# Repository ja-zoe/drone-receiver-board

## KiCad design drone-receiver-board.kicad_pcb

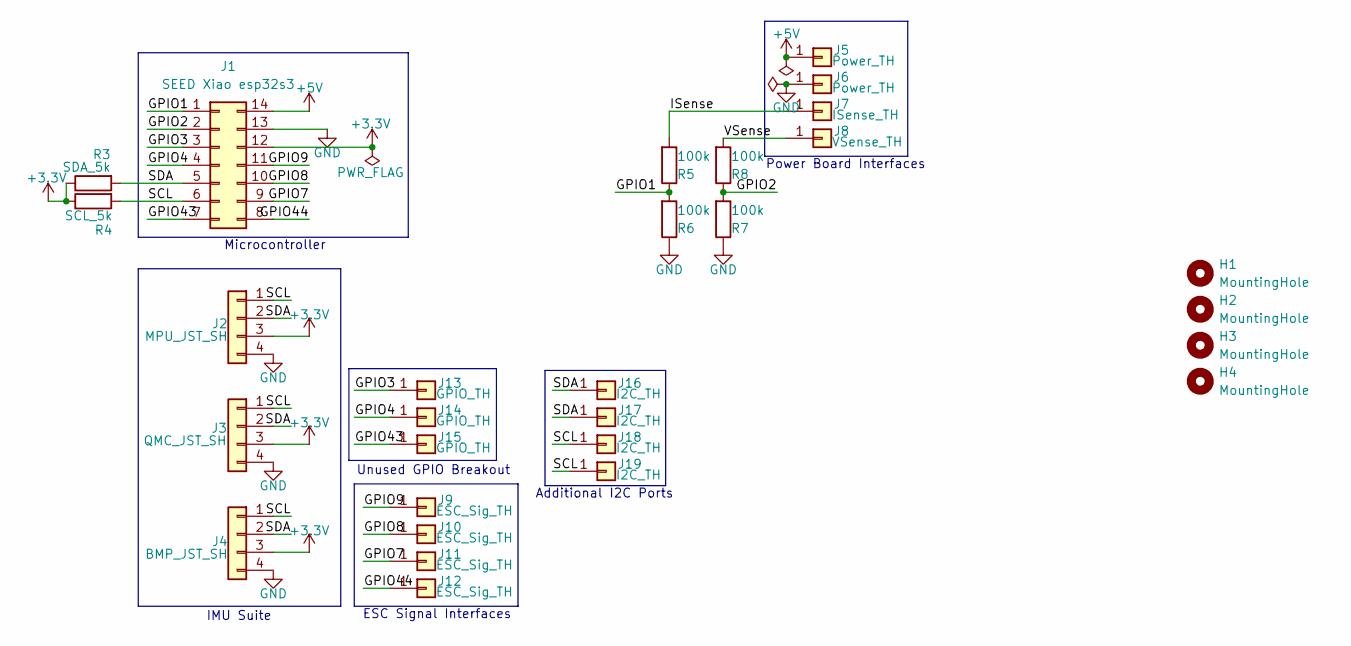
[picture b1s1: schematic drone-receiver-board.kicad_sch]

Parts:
H1, H2, H3, H4: MountingHole; MountingHole_2.2mm_M2
J1: SEED Xiao esp32s3; xiao_esp32c3
J2: MPU_JST_SH; JST_SH_SM04B-SRSS-TB_1x04-1MP_P1.00mm_Horizontal
J3: QMC_JST_SH; JST_SH_SM04B-SRSS-TB_1x04-1MP_P1.00mm_Horizontal
J4: BMP_JST_SH; JST_SH_SM04B-SRSS-TB_1x04-1MP_P1.00mm_Horizontal
J5, J6: Power_TH; SolderWire-0.1sqmm_1x01_D0.4mm_OD1mm
J7: ISense_TH; SolderWire-0.1sqmm_1x01_D0.4mm_OD1mm
J8: VSense_TH; SolderWire-0.1sqmm_1x01_D0.4mm_OD1mm
J9, J10, J11, J12: ESC_Sig_TH; SolderWire-0.1sqmm_1x01_D0.4mm_OD1mm
J13, J14, J15: GPIO_TH; SolderWire-0.1sqmm_1x01_D0.4mm_OD1mm
J16, J17, J18, J19: I2C_TH; SolderWire-0.1sqmm_1x01_D0.4mm_OD1mm
R3: SDA_5k; R_0603_1608Metric_Pad0.98x0.95mm_HandSolder
R4: SCL_5k; R_0603_1608Metric_Pad0.98x0.95mm_HandSolder
R5, R6, R7, R8: 100k; R_0603_1608Metric_Pad0.98x0.95mm_HandSolder

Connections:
+3.3V: J1.12, J2.3, J3.3, J4.3, R3.1, R4.1
+5V: J1.14, J5.1
/GPIO1: J1.1, R5.1, R6.2
/GPIO2: J1.2, R7.2, R8.1
/GPIO3: J1.3, J13.1
/GPIO4: J1.4, J14.1
/GPIO7: J1.9, J11.1
/GPIO8: J1.10, J10.1
/GPIO9: J1.11, J9.1
/GPIO43: J1.7, J15.1
/GPIO44: J1.8, J12.1
/ISense: J7.1, R5.2
/SCL: J1.6, J2.1, J3.1, J4.1, J18.1, J19.1, R4.2
/SDA: J1.5, J2.2, J3.2, J4.2, J16.1, J17.1, R3.2
/VSense: J8.1, R8.2
GND: J1.13, J2.4, J3.4, J4.4, J6.1, R6.1, R7.1

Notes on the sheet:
Unused GPIO Breakout
IMU Suite
Additional I2C Ports
Power Board Interfaces
ESC Signal Interfaces
Microcontroller

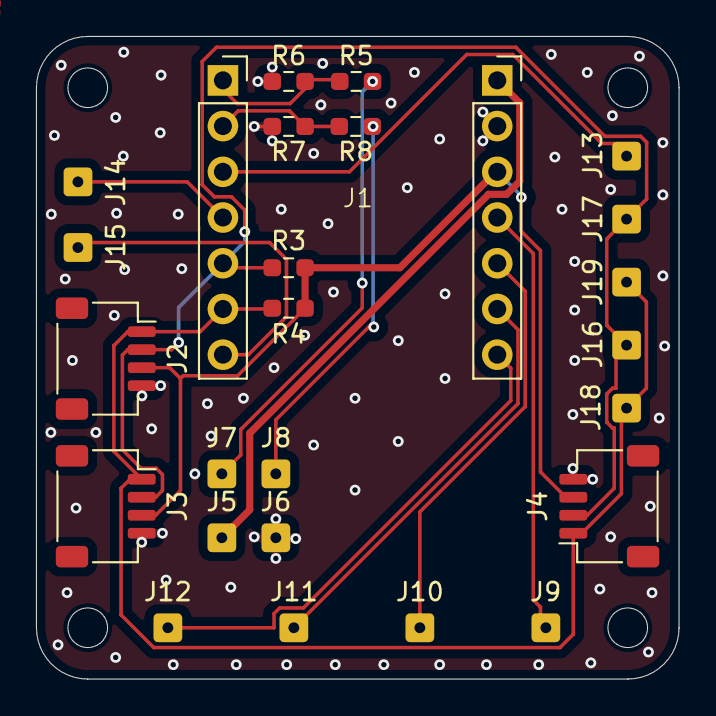
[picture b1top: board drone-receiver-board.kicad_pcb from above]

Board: 2 copper layers, 35.7 x 35.7 mm, 29 parts (0 on the bottom side), 16 nets.

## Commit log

2026-04-03 Add gitignore
2026-04-03 Update tracked files to adhere to gitignore
2026-04-03 Untrack build
2026-04-03 Untrack backups
